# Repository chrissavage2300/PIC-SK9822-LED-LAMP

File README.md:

# PIC-SK9822-LED-LAMP
An LED Lamp Based on the SK9822 LEDs. Also included in this rep is a WS2812 Version.
Both versions were made with KiCad.

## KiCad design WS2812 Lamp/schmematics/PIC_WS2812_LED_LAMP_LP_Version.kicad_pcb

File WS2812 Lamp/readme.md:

This project uses WS2812 LED's. I have not built this one but it should work if you got WS2812 code working.

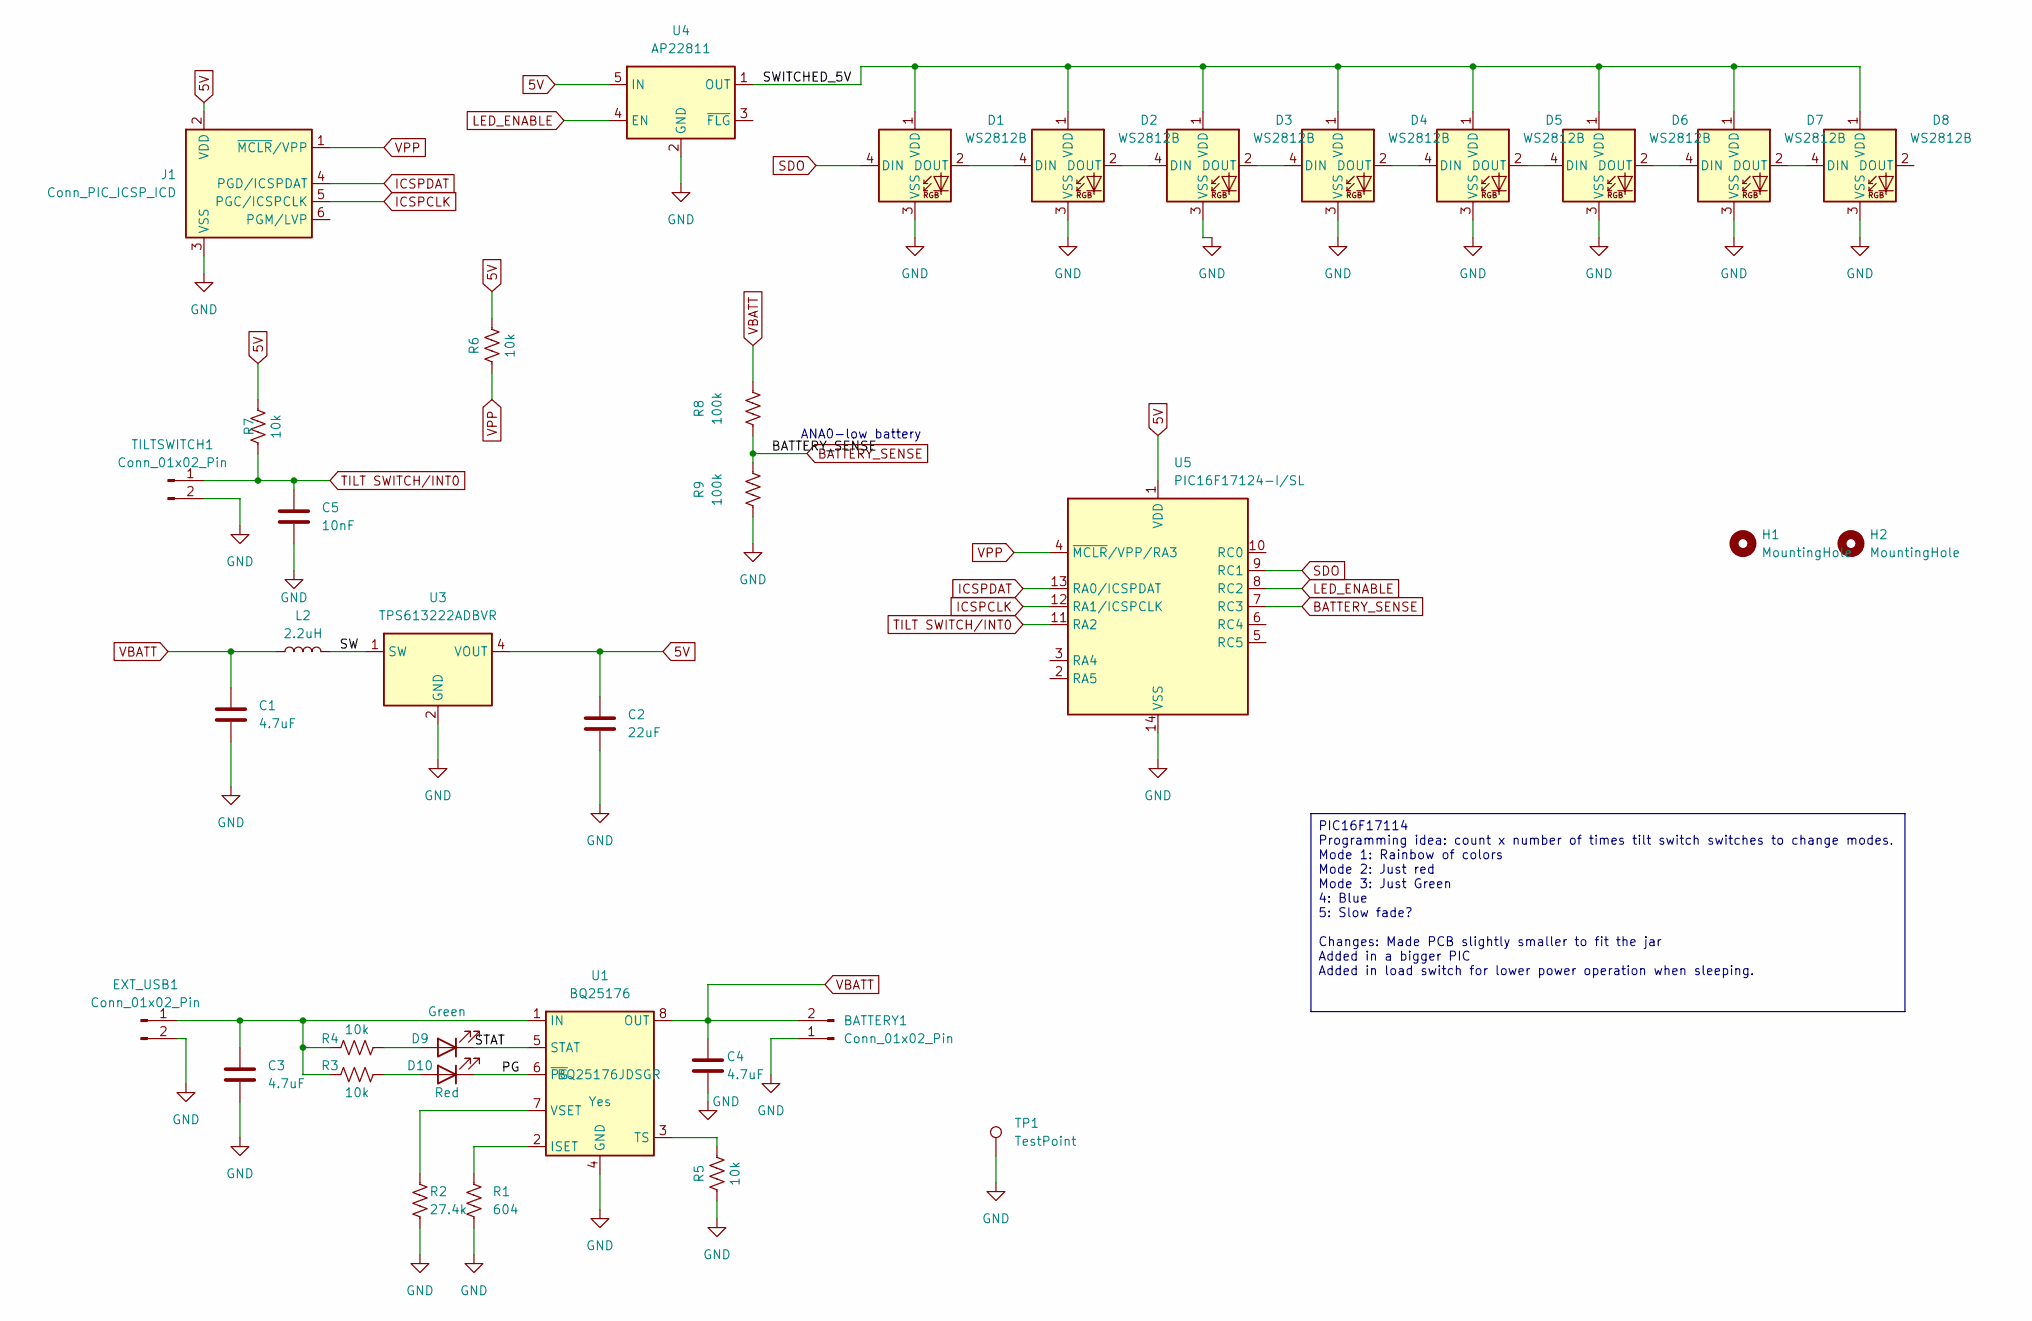
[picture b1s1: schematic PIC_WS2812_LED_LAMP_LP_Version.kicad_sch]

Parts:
BATTERY1: Conn_01x02_Pin; JST_PH_B2B-PH-K_1x02_P2.00mm_Vertical; Mouser Part Number B2B-PH-K-S-GW
C1: 4.7uF; C_1206_3216Metric_Pad1.33x1.80mm_HandSolder; Mouser Part Number 1276-3177-1-ND
C2: 22uF; C_1206_3216Metric_Pad1.33x1.80mm_HandSolder; Mouser Part Number 1276-1287-1-ND
C3, C4: 4.7uF; C_0805_2012Metric_Pad1.18x1.45mm_HandSolder; Mouser Part Number 1276-3177-1-ND
C5: 10nF; C_1206_3216Metric_Pad1.33x1.80mm_HandSolder; Mouser Part Number C1206X103KDRACTU
D1, D2, D3, D4, D5, D6, D7, D8: WS2812B; LED_WS2812B_PLCC4_5.0x5.0mm_P3.2mm
D9: Green; LED_1206_3216Metric_Pad1.42x1.75mm_HandSolder; Mouser Part Number 150120VS75000
D10: Red; LED_1206_3216Metric_Pad1.42x1.75mm_HandSolder; Mouser Part Number 150120RS75000
EXT_USB1: Conn_01x02_Pin; PinHeader_1x02_P2.54mm_Vertical; Mouser Part Number NA
H1, H2: MountingHole; MountingHole_3.2mm_M3
J1: Conn_PIC_ICSP_ICD; PinHeader_1x06_P2.54mm_Vertical; Mouser Part Number xx
L2: 2.2uH; C_0805_2012Metric; Mouser Part Number SRP2010-2R2M
R1: 604; R_1206_3216Metric_Pad1.30x1.75mm_HandSolder; Mouser Part Number CR1206-FX-6040ELF
R2: 27.4k; R_1206_3216Metric_Pad1.30x1.75mm_HandSolder; Mouser Part Number AC1206FR-0727K4L
R3, R4, R5, R6, R7: 10k; R_1206_3216Metric_Pad1.30x1.75mm_HandSolder; Mouser Part Number GENERIC
R8, R9: 100k; R_1206_3216Metric_Pad1.30x1.75mm_HandSolder; Mouser Part Number GENERIC
TILTSWITCH1: Conn_01x02_Pin; PinHeader_1x02_P2.54mm_Vertical; Mouser Part Number NA
TP1: TestPoint; PinHeader_1x01_P2.54mm_Vertical
U1: BQ25176; WSON-8-1EP_2x2mm_P0.5mm_EP0.9x1.6mm; Mouser Part Number BQ25176JDSGR
U3: TPS613222ADBVR; SOT-23-5; Mouser Part Number TPS613222ADBVR
U4: AP22811; SOT-23-5
U5: PIC16F17124-I/SL; SO-14_3.9x8.65mm_P1.27mm

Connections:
5V: C2.1, J1.2 (VDD), R6.2, R7.2, U3.4 (VOUT), U4.5 (IN), U5.1 (VDD)
/PG: D10.1 (K), U1.6 (~PG)
/STAT: D9.1 (K), U1.5 (STAT)
/SW: L2.2, U3.1 (SW)
/SWITCHED_5V: D1.1 (VDD), D2.1 (VDD), D3.1 (VDD), D4.1 (VDD), D5.1 (VDD), D6.1 (VDD), D7.1 (VDD), D8.1 (VDD), U4.1 (OUT)
BATTERY_SENSE: R8.1, R9.2, U5.7 (RC3)
GND: BATTERY1.1, C1.2, C2.2, C3.2, C4.2, C5.2, D1.3 (VSS), D2.3 (VSS), D3.3 (VSS), D4.3 (VSS), D5.3 (VSS), D6.3 (VSS), D7.3 (VSS), D8.3 (VSS), EXT_USB1.2, J1.3 (VSS), R1.2, R2.2, R5.1, R9.1, TILTSWITCH1.2, TP1.1, U1.4 (GND), U1.9 (GND), U3.2 (GND), U4.2 (GND), U5.14 (VSS)
ICSPCLK: J1.5 (PGC/ICSPCLK), U5.12 (RA1/ICSPCLK)
ICSPDAT: J1.4 (PGD/ICSPDAT), U5.13 (RA0/ICSPDAT)
LED_ENABLE: U4.4 (EN), U5.8 (RC2)
unnamed: D1.2 (DOUT), D2.4 (DIN)
unnamed: D2.2 (DOUT), D3.4 (DIN)
unnamed: D3.2 (DOUT), D4.4 (DIN)
unnamed: D4.2 (DOUT), D5.4 (DIN)
unnamed: D5.2 (DOUT), D6.4 (DIN)
unnamed: D6.2 (DOUT), D7.4 (DIN)
unnamed: D7.2 (DOUT), D8.4 (DIN)
unnamed: D9.2 (A), R4.2
unnamed: D10.2 (A), R3.2
unnamed: C3.1, EXT_USB1.1, R3.1, R4.1, U1.1 (IN)
unnamed: R1.1, U1.2 (ISET)
unnamed: R5.2, U1.3 (TS)
unnamed: R2.1, U1.7 (VSET)
SDO: D1.4 (DIN), U5.9 (RC1)
TILT SWITCH/INT0: C5.1, R7.1, TILTSWITCH1.1, U5.11 (RA2)
VBATT: BATTERY1.2, C1.1, C4.1, L2.1, R8.2, U1.8 (OUT)
VPP: J1.1 (~MCLR/VPP), R6.1, U5.4 (~MCLR/VPP/RA3)

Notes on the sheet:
ANA0-low battery
PIC16F17114 Programming idea: count x number of times tilt switch switches to change modes. Mode 1: Rainbow of colors Mode 2: Just red Mode 3: Just Green 4: Blue 5: Slow fade? Changes: Made PCB slightly smaller to fit the jar Added in a bigger PIC Added in load switch for lower power operation when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

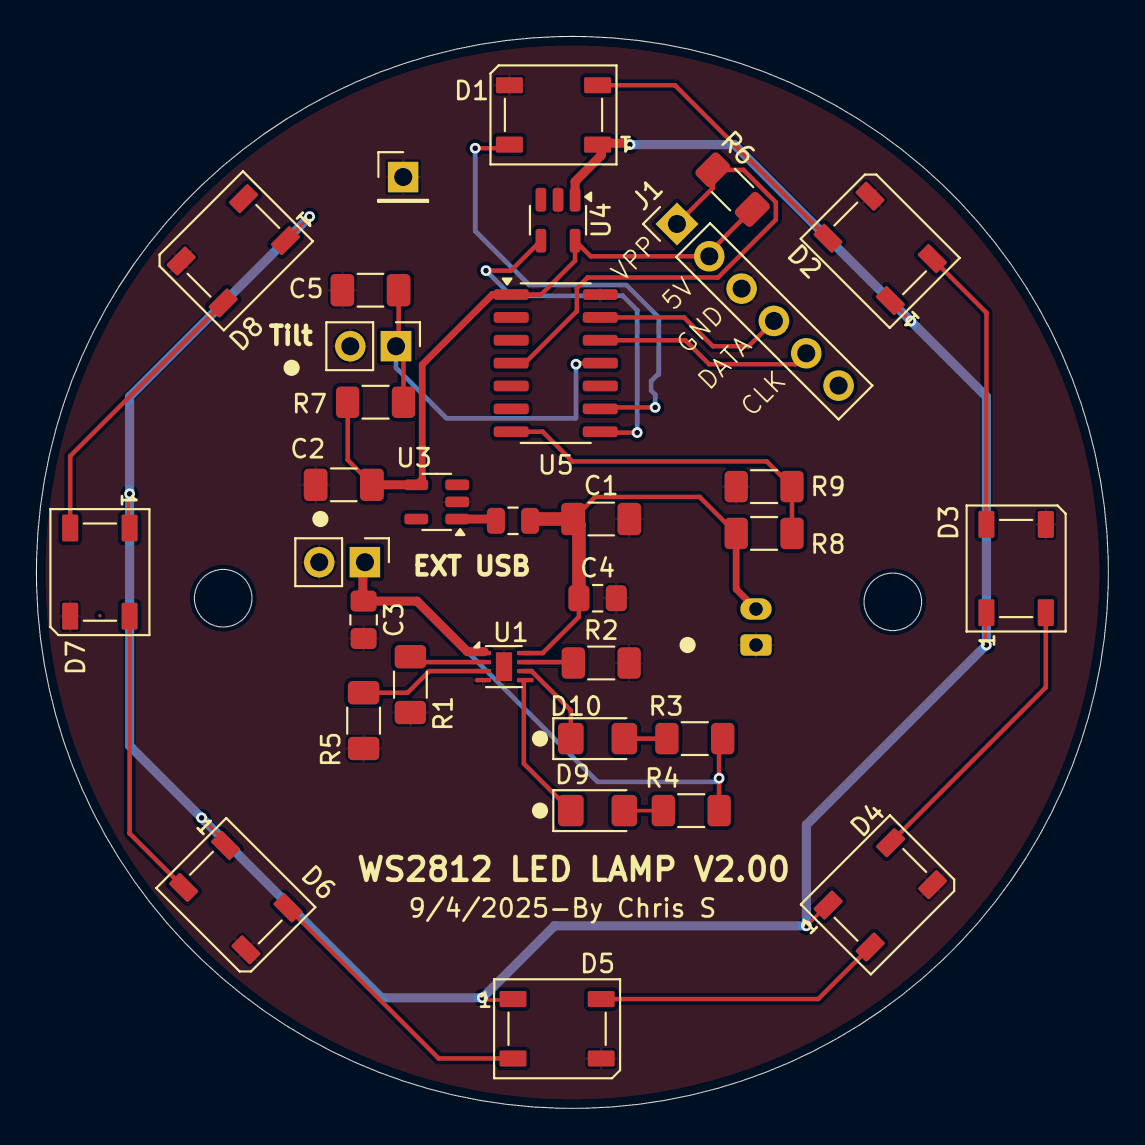
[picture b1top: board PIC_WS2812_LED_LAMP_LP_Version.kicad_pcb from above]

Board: 2 copper layers, 59.6 x 59.6 mm, 36 parts (1 on the bottom side), 27 nets.

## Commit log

2026-02-20 Rename readme.me to readme.md
